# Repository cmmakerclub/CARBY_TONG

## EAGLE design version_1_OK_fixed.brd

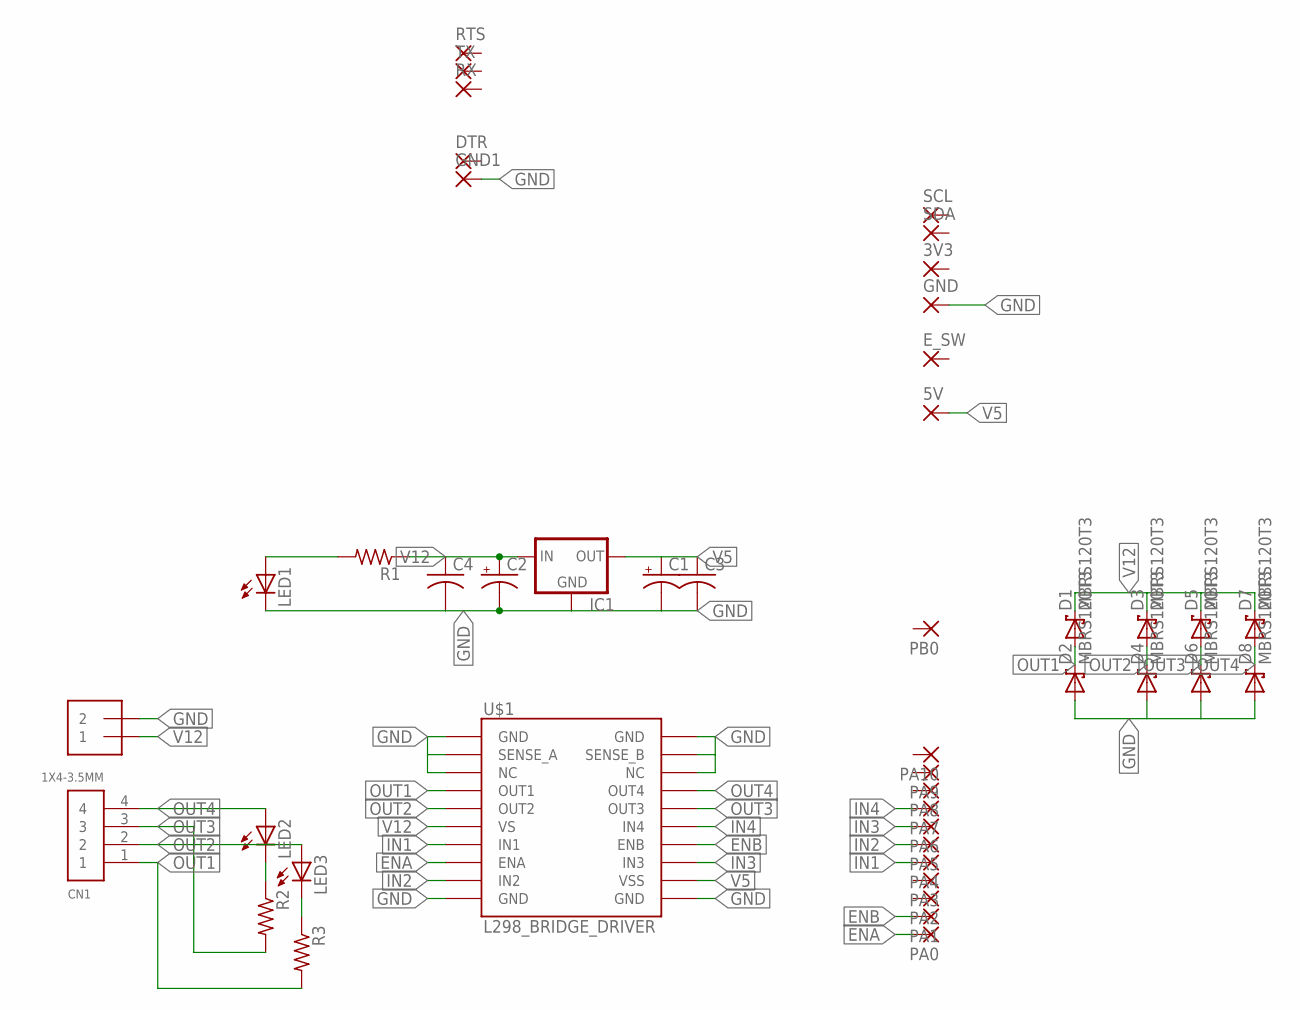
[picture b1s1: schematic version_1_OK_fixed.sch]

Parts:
3V3, 5V: 1,6/0,9
C1: CPOL-USA/3216-18R; A/3216-18R
C2: CPOL-USCT7343; CT7343
C3, C4: C-USC0805; C0805
CN1: 1X4-3.5MM; 1X04-3.5MM
D1, D2, D3, D4, D5, D6, D7, D8: MBRS120T3; DO214AA
DTR: 1,6/0,9
E_SW: 1,6/0,9
GND: 1,6/0,8
GND1: 1,6/0,9
IC1: LM1117; SOT223
J1: 1X2-3.5MM
LED1, LED2, LED3: LEDSMT1206; 1206
PA0, PA1, PA2, PA3, PA4, PA5, PA6, PA7, PA8, PA9, PA10: 1,6/0,9
PB0: 1,6/0,9
R1, R2, R3: R-US_R0805; R0805
RTS: 1,6/0,9
RX: 1,6/0,9
SCL: 1,6/0,9
SDA: 1,6/0,9
TX: 1,6/0,9
U$1: L298_BRIDGE_DRIVER; POWERSO20

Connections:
ENA: PA0.1, U$1.P$8 (ENA)
ENB: PA1.1, U$1.P$14 (ENB)
GND: C1.-, C2.-, C3.2, C4.2, D2.A, D4.A, D6.A, D8.A, GND.1, GND1.1, IC1.1 (GND), J1.2, LED1.C, U$1.P$1 (GND), U$1.P$2 (SENSE_A), U$1.P$3 (NC), U$1.P$10 (GND), U$1.P$11 (GND), U$1.P$18 (NC), U$1.P$19 (SENSE_B), U$1.P$20 (GND)
IN1: PA4.1, U$1.P$7 (IN1)
IN2: PA5.1, U$1.P$9 (IN2)
IN3: PA6.1, U$1.P$13 (IN3)
IN4: PA7.1, U$1.P$15 (IN4)
unnamed: LED1.A, R1.2
unnamed: LED2.C, R2.1
unnamed: LED3.C, R3.1
OUT1: CN1.1, D1.A, D2.C, R3.2, U$1.P$4 (OUT1)
OUT2: CN1.2, D3.A, D4.C, LED3.A, U$1.P$5 (OUT2)
OUT3: CN1.3, D5.A, D6.C, R2.2, U$1.P$16 (OUT3)
OUT4: CN1.4, D7.A, D8.C, LED2.A, U$1.P$17 (OUT4)
V5: 5V.1, C1.+, C3.1, IC1.2 (OUT), U$1.P$12 (VSS)
V12: C2.+, C4.1, D1.C, D3.C, D5.C, D7.C, IC1.3 (IN), J1.1, R1.1, U$1.P$6 (VS)

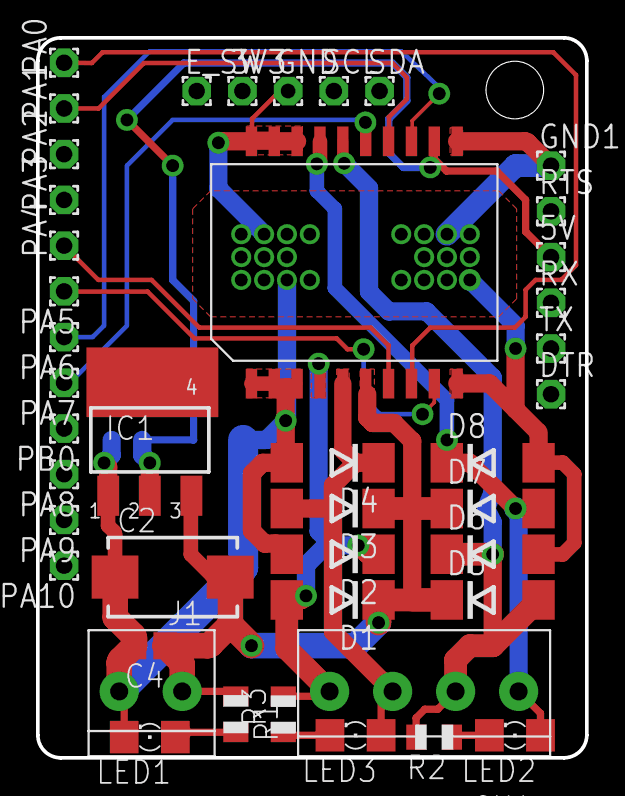
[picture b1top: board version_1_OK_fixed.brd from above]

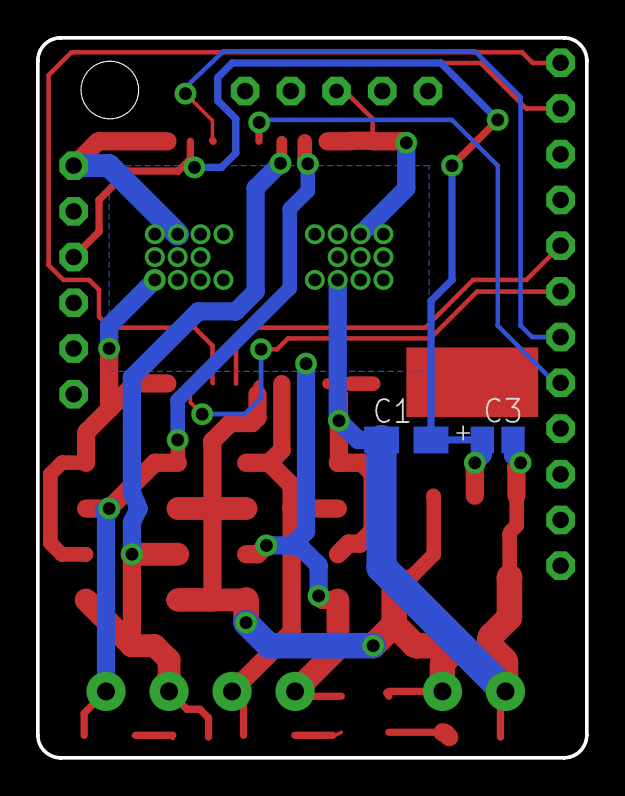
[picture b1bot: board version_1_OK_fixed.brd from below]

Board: 2 copper layers, 30.5 x 40.0 mm, 45 parts (2 on the bottom side), 16 nets.

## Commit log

2016-01-26 ADD1
2016-02-03 fbfbfb
